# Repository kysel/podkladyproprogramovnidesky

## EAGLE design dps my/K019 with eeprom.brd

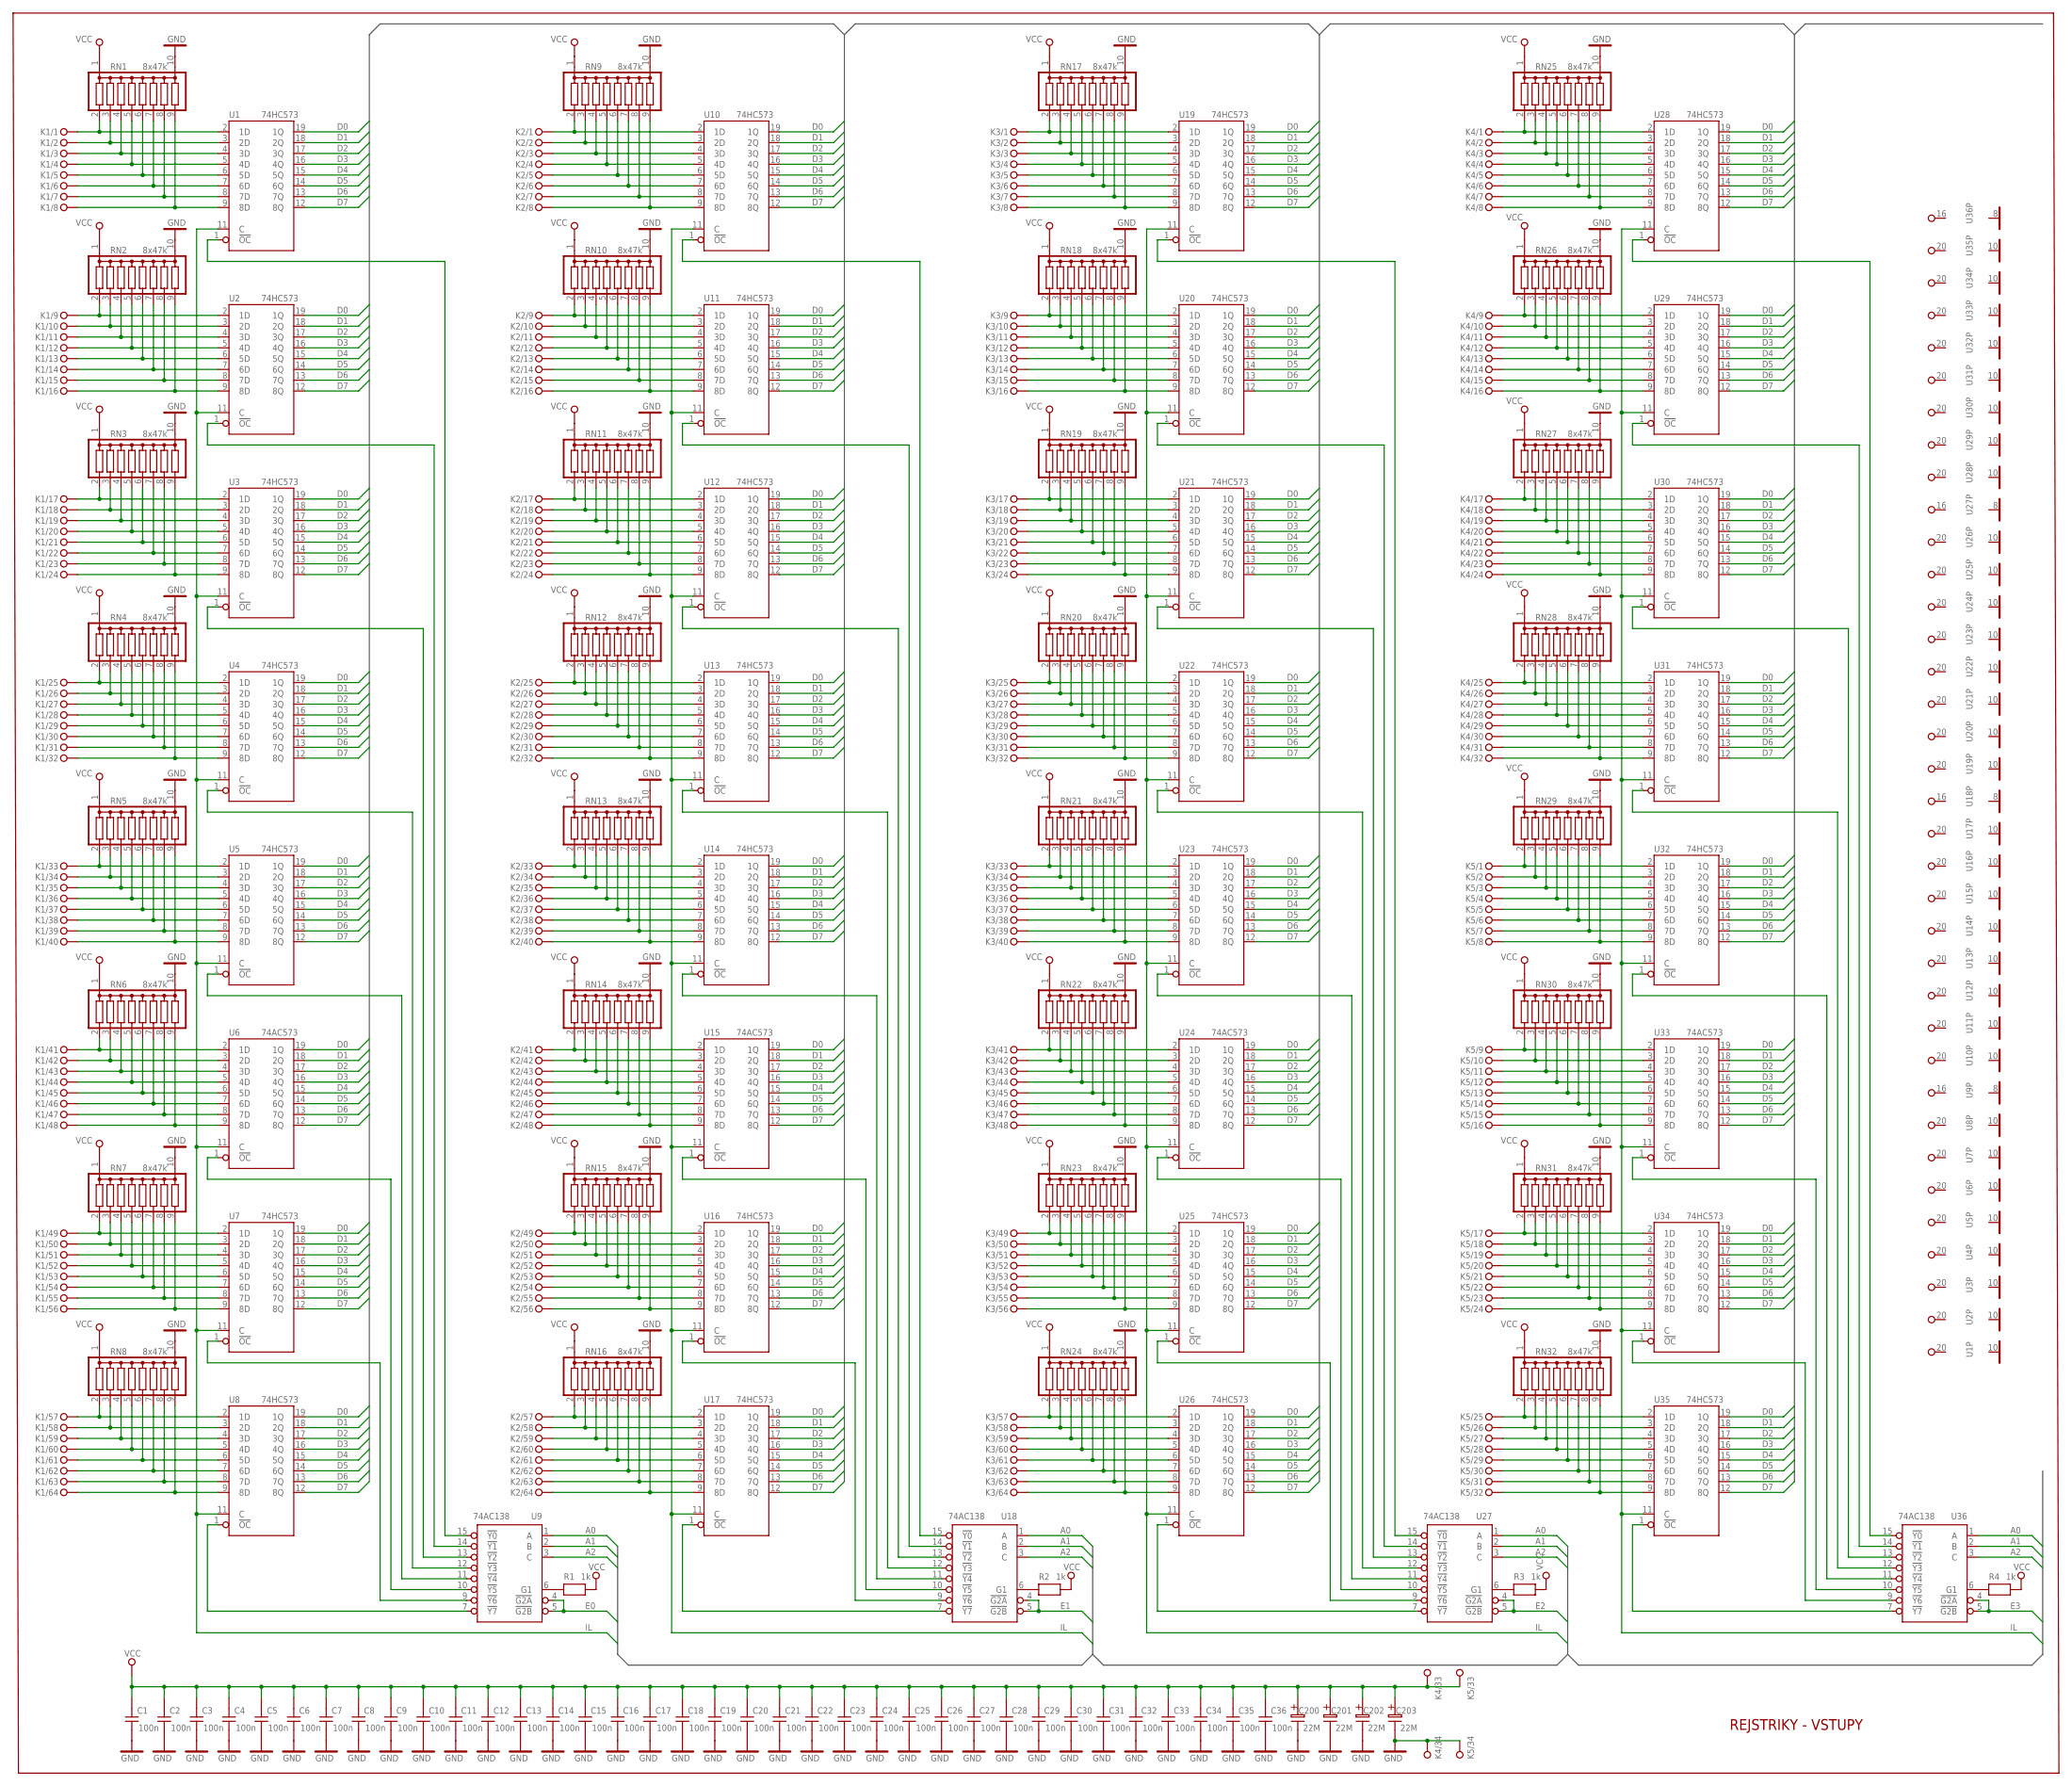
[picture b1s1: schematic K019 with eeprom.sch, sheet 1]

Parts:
C1, C2, C3, C4, C5, C6, C7, C8, C9, C10, C11, C12, C13, C14, C15, C16, C17, C18, C19, C20, C21, C22, C23, C24, C25, C26, C27, C28, C29, C30, C31, C32, C33, C34, C35, C36: 100n; C-5-2X8
C200, C201, C202, C203: 22M; EC-2/5
K1, K2, K3: KON64
K4, K5: KON34
R1, R2, R3, R4: 1k; R-7,5
RN1, RN2, RN3, RN9, RN10, RN11, RN12, RN13, RN14, RN15, RN16, RN17, RN18, RN19, RN20, RN21, RN22, RN23, RN24, RN25, RN26, RN27, RN28, RN29, RN30, RN31, RN32: 8x47k; G08R+@3
RN4, RN5, RN6, RN7, RN8: 8x47k; G08R+@4
U1, U2, U3, U4, U5, U7, U8, U10, U11, U12, U13, U14, U16, U17, U19, U20, U21, U22, U23, U25, U26, U28, U29, U30, U31, U32, U34, U35: 74HC573; DIL20
U6, U15, U24, U33: 74AC573; DIL20
U9, U18, U27, U36: 74AC138; DIL16

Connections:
A0: U9.1 (A), U18.1 (A), U27.1 (A), U36.1 (A); also elsewhere on the board
A1: U9.2 (B), U18.2 (B), U27.2 (B), U36.2 (B); also elsewhere on the board
A2: U9.3 (C), U18.3 (C), U27.3 (C), U36.3 (C); also elsewhere on the board
D0: U1.19 (1Q), U2.19 (1Q), U3.19 (1Q), U4.19 (1Q), U5.19 (1Q), U6.19 (1Q), U7.19 (1Q), U8.19 (1Q), U10.19 (1Q), U11.19 (1Q), U12.19 (1Q), U13.19 (1Q), U14.19 (1Q), U15.19 (1Q), U16.19 (1Q), U17.19 (1Q), U19.19 (1Q), U20.19 (1Q), U21.19 (1Q), U22.19 (1Q), U23.19 (1Q), U24.19 (1Q), U25.19 (1Q), U26.19 (1Q), U28.19 (1Q), U29.19 (1Q), U30.19 (1Q), U31.19 (1Q), U32.19 (1Q), U33.19 (1Q), U34.19 (1Q), U35.19 (1Q); also elsewhere on the board
D1: U1.18 (2Q), U2.18 (2Q), U3.18 (2Q), U4.18 (2Q), U5.18 (2Q), U6.18 (2Q), U7.18 (2Q), U8.18 (2Q), U10.18 (2Q), U11.18 (2Q), U12.18 (2Q), U13.18 (2Q), U14.18 (2Q), U15.18 (2Q), U16.18 (2Q), U17.18 (2Q), U19.18 (2Q), U20.18 (2Q), U21.18 (2Q), U22.18 (2Q), U23.18 (2Q), U24.18 (2Q), U25.18 (2Q), U26.18 (2Q), U28.18 (2Q), U29.18 (2Q), U30.18 (2Q), U31.18 (2Q), U32.18 (2Q), U33.18 (2Q), U34.18 (2Q), U35.18 (2Q); also elsewhere on the board
D2: U1.17 (3Q), U2.17 (3Q), U3.17 (3Q), U4.17 (3Q), U5.17 (3Q), U6.17 (3Q), U7.17 (3Q), U8.17 (3Q), U10.17 (3Q), U11.17 (3Q), U12.17 (3Q), U13.17 (3Q), U14.17 (3Q), U15.17 (3Q), U16.17 (3Q), U17.17 (3Q), U19.17 (3Q), U20.17 (3Q), U21.17 (3Q), U22.17 (3Q), U23.17 (3Q), U24.17 (3Q), U25.17 (3Q), U26.17 (3Q), U28.17 (3Q), U29.17 (3Q), U30.17 (3Q), U31.17 (3Q), U32.17 (3Q), U33.17 (3Q), U34.17 (3Q), U35.17 (3Q); also elsewhere on the board
D3: U1.16 (4Q), U2.16 (4Q), U3.16 (4Q), U4.16 (4Q), U5.16 (4Q), U6.16 (4Q), U7.16 (4Q), U8.16 (4Q), U10.16 (4Q), U11.16 (4Q), U12.16 (4Q), U13.16 (4Q), U14.16 (4Q), U15.16 (4Q), U16.16 (4Q), U17.16 (4Q), U19.16 (4Q), U20.16 (4Q), U21.16 (4Q), U22.16 (4Q), U23.16 (4Q), U24.16 (4Q), U25.16 (4Q), U26.16 (4Q), U28.16 (4Q), U29.16 (4Q), U30.16 (4Q), U31.16 (4Q), U32.16 (4Q), U33.16 (4Q), U34.16 (4Q), U35.16 (4Q); also elsewhere on the board
D4: U1.15 (5Q), U2.15 (5Q), U3.15 (5Q), U4.15 (5Q), U5.15 (5Q), U6.15 (5Q), U7.15 (5Q), U8.15 (5Q), U10.15 (5Q), U11.15 (5Q), U12.15 (5Q), U13.15 (5Q), U14.15 (5Q), U15.15 (5Q), U16.15 (5Q), U17.15 (5Q), U19.15 (5Q), U20.15 (5Q), U21.15 (5Q), U22.15 (5Q), U23.15 (5Q), U24.15 (5Q), U25.15 (5Q), U26.15 (5Q), U28.15 (5Q), U29.15 (5Q), U30.15 (5Q), U31.15 (5Q), U32.15 (5Q), U33.15 (5Q), U34.15 (5Q), U35.15 (5Q); also elsewhere on the board
D5: U1.14 (6Q), U2.14 (6Q), U3.14 (6Q), U4.14 (6Q), U5.14 (6Q), U6.14 (6Q), U7.14 (6Q), U8.14 (6Q), U10.14 (6Q), U11.14 (6Q), U12.14 (6Q), U13.14 (6Q), U14.14 (6Q), U15.14 (6Q), U16.14 (6Q), U17.14 (6Q), U19.14 (6Q), U20.14 (6Q), U21.14 (6Q), U22.14 (6Q), U23.14 (6Q), U24.14 (6Q), U25.14 (6Q), U26.14 (6Q), U28.14 (6Q), U29.14 (6Q), U30.14 (6Q), U31.14 (6Q), U32.14 (6Q), U33.14 (6Q), U34.14 (6Q), U35.14 (6Q); also elsewhere on the board
D6: U1.13 (7Q), U2.13 (7Q), U3.13 (7Q), U4.13 (7Q), U5.13 (7Q), U6.13 (7Q), U7.13 (7Q), U8.13 (7Q), U10.13 (7Q), U11.13 (7Q), U12.13 (7Q), U13.13 (7Q), U14.13 (7Q), U15.13 (7Q), U16.13 (7Q), U17.13 (7Q), U19.13 (7Q), U20.13 (7Q), U21.13 (7Q), U22.13 (7Q), U23.13 (7Q), U24.13 (7Q), U25.13 (7Q), U26.13 (7Q), U28.13 (7Q), U29.13 (7Q), U30.13 (7Q), U31.13 (7Q), U32.13 (7Q), U33.13 (7Q), U34.13 (7Q), U35.13 (7Q); also elsewhere on the board
D7: U1.12 (8Q), U2.12 (8Q), U3.12 (8Q), U4.12 (8Q), U5.12 (8Q), U6.12 (8Q), U7.12 (8Q), U8.12 (8Q), U10.12 (8Q), U11.12 (8Q), U12.12 (8Q), U13.12 (8Q), U14.12 (8Q), U15.12 (8Q), U16.12 (8Q), U17.12 (8Q), U19.12 (8Q), U20.12 (8Q), U21.12 (8Q), U22.12 (8Q), U23.12 (8Q), U24.12 (8Q), U25.12 (8Q), U26.12 (8Q), U28.12 (8Q), U29.12 (8Q), U30.12 (8Q), U31.12 (8Q), U32.12 (8Q), U33.12 (8Q), U34.12 (8Q), U35.12 (8Q); also elsewhere on the board
E0: U9.4 (!G2A), U9.5 (!G2B); also elsewhere on the board
E1: U18.4 (!G2A), U18.5 (!G2B); also elsewhere on the board
E2: U27.4 (!G2A), U27.5 (!G2B); also elsewhere on the board
E3: U36.4 (!G2A), U36.5 (!G2B); also elsewhere on the board
GND: C1.1, C2.1, C3.1, C4.1, C5.1, C6.1, C7.1, C8.1, C9.1, C10.1, C11.1, C12.1, C13.1, C14.1, C15.1, C16.1, C17.1, C18.1, C19.1, C20.1, C21.1, C22.1, C23.1, C24.1, C25.1, C26.1, C27.1, C28.1, C29.1, C30.1, C31.1, C32.1, C33.1, C34.1, C35.1, C36.1, C200.1, C201.1, C202.1, C203.1, K4.34, K5.34, RN1.10, RN2.10, RN3.10, RN4.10, RN5.10, RN6.10, RN7.10, RN8.10, RN9.10, RN10.10, RN11.10, RN12.10, RN13.10, RN14.10, RN15.10, RN16.10, RN17.10, RN18.10, RN19.10, RN20.10, RN21.10, RN22.10, RN23.10, RN24.10, RN25.10, RN26.10, RN27.10, RN28.10, RN29.10, RN30.10, RN31.10, RN32.10, U1.10 (GND), U2.10 (GND), U3.10 (GND), U4.10 (GND), U5.10 (GND), U6.10 (GND), U7.10 (GND), U8.10 (GND), U9.8 (GND), U10.10 (GND), U11.10 (GND), U12.10 (GND), U13.10 (GND), U14.10 (GND), U15.10 (GND), U16.10 (GND), U17.10 (GND), U18.8 (GND), U19.10 (GND), U20.10 (GND), U21.10 (GND), U22.10 (GND), U23.10 (GND), U24.10 (GND), U25.10 (GND), U26.10 (GND), U27.8 (GND), U28.10 (GND), U29.10 (GND), U30.10 (GND), U31.10 (GND), U32.10 (GND), U33.10 (GND), U34.10 (GND), U35.10 (GND), U36.8 (GND); also elsewhere on the board
IL: U1.11 (C), U2.11 (C), U3.11 (C), U4.11 (C), U5.11 (C), U6.11 (C), U7.11 (C), U8.11 (C), U10.11 (C), U11.11 (C), U12.11 (C), U13.11 (C), U14.11 (C), U15.11 (C), U16.11 (C), U17.11 (C), U19.11 (C), U20.11 (C), U21.11 (C), U22.11 (C), U23.11 (C), U24.11 (C), U25.11 (C), U26.11 (C), U28.11 (C), U29.11 (C), U30.11 (C), U31.11 (C), U32.11 (C), U33.11 (C), U34.11 (C), U35.11 (C); also elsewhere on the board
unnamed: U8.1 (!OC), U9.7 (!Y7)
unnamed: U7.1 (!OC), U9.9 (!Y6)
unnamed: U6.1 (!OC), U9.10 (!Y5)
unnamed: U5.1 (!OC), U9.11 (!Y4)
unnamed: U4.1 (!OC), U9.12 (!Y3)
unnamed: U3.1 (!OC), U9.13 (!Y2)
unnamed: U2.1 (!OC), U9.14 (!Y1)
unnamed: U1.1 (!OC), U9.15 (!Y0)
unnamed: U26.1 (!OC), U27.7 (!Y7)
unnamed: K1.1, RN1.2, U1.2 (1D)
unnamed: K1.2, RN1.3, U1.3 (2D)
unnamed: K1.3, RN1.4, U1.4 (3D)
unnamed: K1.4, RN1.5, U1.5 (4D)
unnamed: K1.5, RN1.6, U1.6 (5D)
unnamed: K1.6, RN1.7, U1.7 (6D)
unnamed: K1.7, RN1.8, U1.8 (7D)
unnamed: K1.8, RN1.9, U1.9 (8D)
unnamed: K1.9, RN2.2, U2.2 (1D)
unnamed: K1.10, RN2.3, U2.3 (2D)
unnamed: K1.11, RN2.4, U2.4 (3D)
unnamed: K1.12, RN2.5, U2.5 (4D)
unnamed: K1.13, RN2.6, U2.6 (5D)
unnamed: K1.14, RN2.7, U2.7 (6D)
unnamed: K1.15, RN2.8, U2.8 (7D)
unnamed: K1.16, RN2.9, U2.9 (8D)
unnamed: K1.17, RN3.2, U3.2 (1D)
unnamed: K1.18, RN3.3, U3.3 (2D)
unnamed: K1.19, RN3.4, U3.4 (3D)
unnamed: K1.20, RN3.5, U3.5 (4D)
unnamed: K1.21, RN3.6, U3.6 (5D)
unnamed: K1.22, RN3.7, U3.7 (6D)
unnamed: K1.23, RN3.8, U3.8 (7D)
unnamed: K1.24, RN3.9, U3.9 (8D)
unnamed: K1.25, RN4.2, U4.2 (1D)
unnamed: K1.26, RN4.3, U4.3 (2D)
unnamed: K1.27, RN4.4, U4.4 (3D)
unnamed: K1.28, RN4.5, U4.5 (4D)
unnamed: K1.29, RN4.6, U4.6 (5D)
unnamed: K1.30, RN4.7, U4.7 (6D)
unnamed: K1.31, RN4.8, U4.8 (7D)
unnamed: K1.32, RN4.9, U4.9 (8D)
unnamed: K1.33, RN5.2, U5.2 (1D)
unnamed: K1.34, RN5.3, U5.3 (2D)
unnamed: K1.35, RN5.4, U5.4 (3D)
unnamed: K1.36, RN5.5, U5.5 (4D)
unnamed: K1.37, RN5.6, U5.6 (5D)
unnamed: K1.38, RN5.7, U5.7 (6D)
unnamed: K1.39, RN5.8, U5.8 (7D)
unnamed: K1.40, RN5.9, U5.9 (8D)
unnamed: K1.41, RN6.2, U6.2 (1D)
unnamed: K1.42, RN6.3, U6.3 (2D)
unnamed: K1.43, RN6.4, U6.4 (3D)
unnamed: K1.44, RN6.5, U6.5 (4D)
unnamed: K1.45, RN6.6, U6.6 (5D)
unnamed: K1.46, RN6.7, U6.7 (6D)
unnamed: K1.47, RN6.8, U6.8 (7D)
unnamed: K1.48, RN6.9, U6.9 (8D)
unnamed: K1.49, RN7.2, U7.2 (1D)
unnamed: K1.50, RN7.3, U7.3 (2D)
unnamed: K1.51, RN7.4, U7.4 (3D)
unnamed: K1.52, RN7.5, U7.5 (4D)
unnamed: K1.53, RN7.6, U7.6 (5D)
unnamed: K1.54, RN7.7, U7.7 (6D)
unnamed: K1.55, RN7.8, U7.8 (7D)
unnamed: K1.56, RN7.9, U7.9 (8D)
unnamed: K1.57, RN8.2, U8.2 (1D)
unnamed: K1.58, RN8.3, U8.3 (2D)
unnamed: K1.59, RN8.4, U8.4 (3D)
unnamed: K1.60, RN8.5, U8.5 (4D)
unnamed: K1.61, RN8.6, U8.6 (5D)
unnamed: K1.62, RN8.7, U8.7 (6D)
unnamed: K1.63, RN8.8, U8.8 (7D)
unnamed: K1.64, RN8.9, U8.9 (8D)
unnamed: U17.1 (!OC), U18.7 (!Y7)
unnamed: U16.1 (!OC), U18.9 (!Y6)
unnamed: U15.1 (!OC), U18.10 (!Y5)
unnamed: U14.1 (!OC), U18.11 (!Y4)
unnamed: U13.1 (!OC), U18.12 (!Y3)
unnamed: U12.1 (!OC), U18.13 (!Y2)
unnamed: U11.1 (!OC), U18.14 (!Y1)
unnamed: U10.1 (!OC), U18.15 (!Y0)
unnamed: U25.1 (!OC), U27.9 (!Y6)
unnamed: K2.1, RN9.2, U10.2 (1D)
unnamed: K2.2, RN9.3, U10.3 (2D)
unnamed: K2.3, RN9.4, U10.4 (3D)
unnamed: K2.4, RN9.5, U10.5 (4D)
unnamed: K2.5, RN9.6, U10.6 (5D)
unnamed: K2.6, RN9.7, U10.7 (6D)
unnamed: K2.7, RN9.8, U10.8 (7D)
unnamed: K2.8, RN9.9, U10.9 (8D)
unnamed: K2.9, RN10.2, U11.2 (1D)
unnamed: K2.10, RN10.3, U11.3 (2D)
unnamed: K2.11, RN10.4, U11.4 (3D)
unnamed: K2.12, RN10.5, U11.5 (4D)
unnamed: K2.13, RN10.6, U11.6 (5D)
unnamed: K2.14, RN10.7, U11.7 (6D)
unnamed: K2.15, RN10.8, U11.8 (7D)
unnamed: K2.16, RN10.9, U11.9 (8D)
unnamed: K2.17, RN11.2, U12.2 (1D)
unnamed: K2.18, RN11.3, U12.3 (2D)
unnamed: K2.19, RN11.4, U12.4 (3D)
unnamed: K2.20, RN11.5, U12.5 (4D)
unnamed: K2.21, RN11.6, U12.6 (5D)
unnamed: K2.22, RN11.7, U12.7 (6D)
unnamed: K2.23, RN11.8, U12.8 (7D)
unnamed: K2.24, RN11.9, U12.9 (8D)
unnamed: K2.25, RN12.2, U13.2 (1D)
unnamed: K2.26, RN12.3, U13.3 (2D)
unnamed: K2.27, RN12.4, U13.4 (3D)
unnamed: K2.28, RN12.5, U13.5 (4D)
unnamed: K2.29, RN12.6, U13.6 (5D)
unnamed: K2.30, RN12.7, U13.7 (6D)
unnamed: K2.31, RN12.8, U13.8 (7D)
unnamed: K2.32, RN12.9, U13.9 (8D)
unnamed: K2.33, RN13.2, U14.2 (1D)
unnamed: K2.34, RN13.3, U14.3 (2D)
unnamed: K2.35, RN13.4, U14.4 (3D)
unnamed: K2.36, RN13.5, U14.5 (4D)
unnamed: K2.37, RN13.6, U14.6 (5D)
unnamed: K2.38, RN13.7, U14.7 (6D)
unnamed: K2.39, RN13.8, U14.8 (7D)
unnamed: K2.40, RN13.9, U14.9 (8D)
unnamed: K2.41, RN14.2, U15.2 (1D)
unnamed: K2.42, RN14.3, U15.3 (2D)
unnamed: K2.43, RN14.4, U15.4 (3D)
unnamed: K2.44, RN14.5, U15.5 (4D)
unnamed: K2.45, RN14.6, U15.6 (5D)
unnamed: K2.46, RN14.7, U15.7 (6D)
unnamed: K2.47, RN14.8, U15.8 (7D)
unnamed: K2.48, RN14.9, U15.9 (8D)
unnamed: K2.49, RN15.2, U16.2 (1D)
unnamed: K2.50, RN15.3, U16.3 (2D)
unnamed: K2.51, RN15.4, U16.4 (3D)
unnamed: K2.52, RN15.5, U16.5 (4D)
unnamed: K2.53, RN15.6, U16.6 (5D)
unnamed: K2.54, RN15.7, U16.7 (6D)
unnamed: K2.55, RN15.8, U16.8 (7D)
unnamed: K2.56, RN15.9, U16.9 (8D)
unnamed: K2.57, RN16.2, U17.2 (1D)
unnamed: K2.58, RN16.3, U17.3 (2D)
unnamed: K2.59, RN16.4, U17.4 (3D)
unnamed: K2.60, RN16.5, U17.5 (4D)
unnamed: K2.61, RN16.6, U17.6 (5D)
unnamed: K2.62, RN16.7, U17.7 (6D)
unnamed: K2.63, RN16.8, U17.8 (7D)
unnamed: K2.64, RN16.9, U17.9 (8D)
unnamed: U24.1 (!OC), U27.10 (!Y5)
unnamed: U23.1 (!OC), U27.11 (!Y4)
unnamed: U22.1 (!OC), U27.12 (!Y3)
unnamed: U21.1 (!OC), U27.13 (!Y2)
unnamed: U20.1 (!OC), U27.14 (!Y1)
unnamed: U19.1 (!OC), U27.15 (!Y0)
unnamed: K3.1, RN17.2, U19.2 (1D)
unnamed: K3.2, RN17.3, U19.3 (2D)
unnamed: K3.3, RN17.4, U19.4 (3D)
unnamed: K3.4, RN17.5, U19.5 (4D)
unnamed: K3.5, RN17.6, U19.6 (5D)
unnamed: K3.6, RN17.7, U19.7 (6D)
unnamed: K3.7, RN17.8, U19.8 (7D)
unnamed: K3.8, RN17.9, U19.9 (8D)
unnamed: K3.9, RN18.2, U20.2 (1D)
unnamed: K3.10, RN18.3, U20.3 (2D)
unnamed: K3.11, RN18.4, U20.4 (3D)
unnamed: K3.12, RN18.5, U20.5 (4D)
unnamed: K3.13, RN18.6, U20.6 (5D)
unnamed: K3.14, RN18.7, U20.7 (6D)
unnamed: K3.15, RN18.8, U20.8 (7D)
unnamed: K3.16, RN18.9, U20.9 (8D)
unnamed: K3.17, RN19.2, U21.2 (1D)
unnamed: K3.18, RN19.3, U21.3 (2D)
unnamed: K3.19, RN19.4, U21.4 (3D)
unnamed: K3.20, RN19.5, U21.5 (4D)
unnamed: K3.21, RN19.6, U21.6 (5D)
unnamed: K3.22, RN19.7, U21.7 (6D)
unnamed: K3.23, RN19.8, U21.8 (7D)
unnamed: K3.24, RN19.9, U21.9 (8D)
unnamed: K3.25, RN20.2, U22.2 (1D)
unnamed: K3.26, RN20.3, U22.3 (2D)
unnamed: K3.27, RN20.4, U22.4 (3D)
unnamed: K3.28, RN20.5, U22.5 (4D)
unnamed: K3.29, RN20.6, U22.6 (5D)
unnamed: K3.30, RN20.7, U22.7 (6D)
unnamed: K3.31, RN20.8, U22.8 (7D)
unnamed: K3.32, RN20.9, U22.9 (8D)
unnamed: K3.33, RN21.2, U23.2 (1D)
unnamed: K3.34, RN21.3, U23.3 (2D)
unnamed: K3.35, RN21.4, U23.4 (3D)
unnamed: K3.36, RN21.5, U23.5 (4D)
unnamed: K3.37, RN21.6, U23.6 (5D)
unnamed: K3.38, RN21.7, U23.7 (6D)
unnamed: K3.39, RN21.8, U23.8 (7D)
unnamed: K3.40, RN21.9, U23.9 (8D)
unnamed: K3.41, RN22.2, U24.2 (1D)
unnamed: K3.42, RN22.3, U24.3 (2D)
unnamed: K3.43, RN22.4, U24.4 (3D)
unnamed: K3.44, RN22.5, U24.5 (4D)
unnamed: K3.45, RN22.6, U24.6 (5D)
unnamed: K3.46, RN22.7, U24.7 (6D)
unnamed: K3.47, RN22.8, U24.8 (7D)
unnamed: K3.48, RN22.9, U24.9 (8D)
unnamed: K3.49, RN23.2, U25.2 (1D)
unnamed: K3.50, RN23.3, U25.3 (2D)
unnamed: K3.51, RN23.4, U25.4 (3D)
unnamed: K3.52, RN23.5, U25.5 (4D)
unnamed: K3.53, RN23.6, U25.6 (5D)
unnamed: K3.54, RN23.7, U25.7 (6D)
unnamed: K3.55, RN23.8, U25.8 (7D)
unnamed: K3.56, RN23.9, U25.9 (8D)
unnamed: K3.57, RN24.2, U26.2 (1D)
unnamed: K3.58, RN24.3, U26.3 (2D)
unnamed: K3.59, RN24.4, U26.4 (3D)
unnamed: K3.60, RN24.5, U26.5 (4D)
unnamed: K3.61, RN24.6, U26.6 (5D)
unnamed: K3.62, RN24.7, U26.7 (6D)
unnamed: K3.63, RN24.8, U26.8 (7D)
unnamed: K3.64, RN24.9, U26.9 (8D)
unnamed: U35.1 (!OC), U36.7 (!Y7)
unnamed: U34.1 (!OC), U36.9 (!Y6)
unnamed: U33.1 (!OC), U36.10 (!Y5)
unnamed: U32.1 (!OC), U36.11 (!Y4)
unnamed: U31.1 (!OC), U36.12 (!Y3)
unnamed: U30.1 (!OC), U36.13 (!Y2)
unnamed: U29.1 (!OC), U36.14 (!Y1)
unnamed: U28.1 (!OC), U36.15 (!Y0)
unnamed: K4.1, RN25.2, U28.2 (1D)
unnamed: K4.2, RN25.3, U28.3 (2D)
unnamed: K4.3, RN25.4, U28.4 (3D)
unnamed: K4.4, RN25.5, U28.5 (4D)
unnamed: K4.5, RN25.6, U28.6 (5D)
unnamed: K4.6, RN25.7, U28.7 (6D)
unnamed: K4.7, RN25.8, U28.8 (7D)
unnamed: K4.8, RN25.9, U28.9 (8D)
unnamed: K4.9, RN26.2, U29.2 (1D)
unnamed: K4.10, RN26.3, U29.3 (2D)
unnamed: K4.11, RN26.4, U29.4 (3D)
unnamed: K4.12, RN26.5, U29.5 (4D)
unnamed: K4.13, RN26.6, U29.6 (5D)
unnamed: K4.14, RN26.7, U29.7 (6D)
unnamed: K4.15, RN26.8, U29.8 (7D)
unnamed: K4.16, RN26.9, U29.9 (8D)
unnamed: K4.17, RN27.2, U30.2 (1D)
unnamed: K4.18, RN27.3, U30.3 (2D)
unnamed: K4.19, RN27.4, U30.4 (3D)
unnamed: K4.20, RN27.5, U30.5 (4D)
unnamed: K4.21, RN27.6, U30.6 (5D)
unnamed: K4.22, RN27.7, U30.7 (6D)
unnamed: K4.23, RN27.8, U30.8 (7D)
unnamed: K4.24, RN27.9, U30.9 (8D)
unnamed: K4.25, RN28.2, U31.2 (1D)
unnamed: K4.26, RN28.3, U31.3 (2D)
unnamed: K4.27, RN28.4, U31.4 (3D)
unnamed: K4.28, RN28.5, U31.5 (4D)
unnamed: K4.29, RN28.6, U31.6 (5D)
unnamed: K4.30, RN28.7, U31.7 (6D)
unnamed: K4.31, RN28.8, U31.8 (7D)
unnamed: K4.32, RN28.9, U31.9 (8D)
unnamed: K5.1, RN29.2, U32.2 (1D)
unnamed: K5.2, RN29.3, U32.3 (2D)
unnamed: K5.3, RN29.4, U32.4 (3D)
unnamed: K5.4, RN29.5, U32.5 (4D)
unnamed: K5.5, RN29.6, U32.6 (5D)
unnamed: K5.6, RN29.7, U32.7 (6D)
unnamed: K5.7, RN29.8, U32.8 (7D)
unnamed: K5.8, RN29.9, U32.9 (8D)
unnamed: K5.9, RN30.2, U33.2 (1D)
unnamed: K5.10, RN30.3, U33.3 (2D)
unnamed: K5.11, RN30.4, U33.4 (3D)
unnamed: K5.12, RN30.5, U33.5 (4D)
unnamed: K5.13, RN30.6, U33.6 (5D)
unnamed: K5.14, RN30.7, U33.7 (6D)
unnamed: K5.15, RN30.8, U33.8 (7D)
unnamed: K5.16, RN30.9, U33.9 (8D)
unnamed: K5.17, RN31.2, U34.2 (1D)
unnamed: K5.18, RN31.3, U34.3 (2D)
unnamed: K5.19, RN31.4, U34.4 (3D)
unnamed: K5.20, RN31.5, U34.5 (4D)
unnamed: K5.21, RN31.6, U34.6 (5D)
unnamed: K5.22, RN31.7, U34.7 (6D)
unnamed: K5.23, RN31.8, U34.8 (7D)
unnamed: K5.24, RN31.9, U34.9 (8D)
unnamed: K5.25, RN32.2, U35.2 (1D)
unnamed: K5.26, RN32.3, U35.3 (2D)
unnamed: K5.27, RN32.4, U35.4 (3D)
unnamed: K5.28, RN32.5, U35.5 (4D)
unnamed: K5.29, RN32.6, U35.6 (5D)
unnamed: K5.30, RN32.7, U35.7 (6D)
unnamed: K5.31, RN32.8, U35.8 (7D)
unnamed: K5.32, RN32.9, U35.9 (8D)
unnamed: R1.1, U9.6 (G1)
unnamed: R2.1, U18.6 (G1)
unnamed: R3.1, U27.6 (G1)
unnamed: R4.1, U36.6 (G1)
VCC: C1.2, C2.2, C3.2, C4.2, C5.2, C6.2, C7.2, C8.2, C9.2, C10.2, C11.2, C12.2, C13.2, C14.2, C15.2, C16.2, C17.2, C18.2, C19.2, C20.2, C21.2, C22.2, C23.2, C24.2, C25.2, C26.2, C27.2, C28.2, C29.2, C30.2, C31.2, C32.2, C33.2, C34.2, C35.2, C36.2, C200.2, C201.2, C202.2, C203.2, K4.33, K5.33, R1.2, R2.2, R3.2, R4.2, RN1.1, RN2.1, RN3.1, RN4.1, RN5.1, RN6.1, RN7.1, RN8.1, RN9.1, RN10.1, RN11.1, RN12.1, RN13.1, RN14.1, RN15.1, RN16.1, RN17.1, RN18.1, RN19.1, RN20.1, RN21.1, RN22.1, RN23.1, RN24.1, RN25.1, RN26.1, RN27.1, RN28.1, RN29.1, RN30.1, RN31.1, RN32.1, U1.20 (VCC), U2.20 (VCC), U3.20 (VCC), U4.20 (VCC), U5.20 (VCC), U6.20 (VCC), U7.20 (VCC), U8.20 (VCC), U9.16 (VCC), U10.20 (VCC), U11.20 (VCC), U12.20 (VCC), U13.20 (VCC), U14.20 (VCC), U15.20 (VCC), U16.20 (VCC), U17.20 (VCC), U18.16 (VCC), U19.20 (VCC), U20.20 (VCC), U21.20 (VCC), U22.20 (VCC), U23.20 (VCC), U24.20 (VCC), U25.20 (VCC), U26.20 (VCC), U27.16 (VCC), U28.20 (VCC), U29.20 (VCC), U30.20 (VCC), U31.20 (VCC), U32.20 (VCC), U33.20 (VCC), U34.20 (VCC), U35.20 (VCC), U36.16 (VCC); also elsewhere on the board

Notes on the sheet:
REJSTRIKY - VSTUPY
